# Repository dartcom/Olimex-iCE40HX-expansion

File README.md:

# Olimex-iCE40HX-expansion
An expansion board for the iCE40HX8K-EVB fpga devkit containing a 24-bit parallel video output, a VGA output and a dual composite input based on the ADV7180 SDTV video decoder.

# Resources
- VGA subsystem is based on the [Digilent Pmod VGA adapter](https://digilent.com/shop/pmod-vga-video-graphics-array/).

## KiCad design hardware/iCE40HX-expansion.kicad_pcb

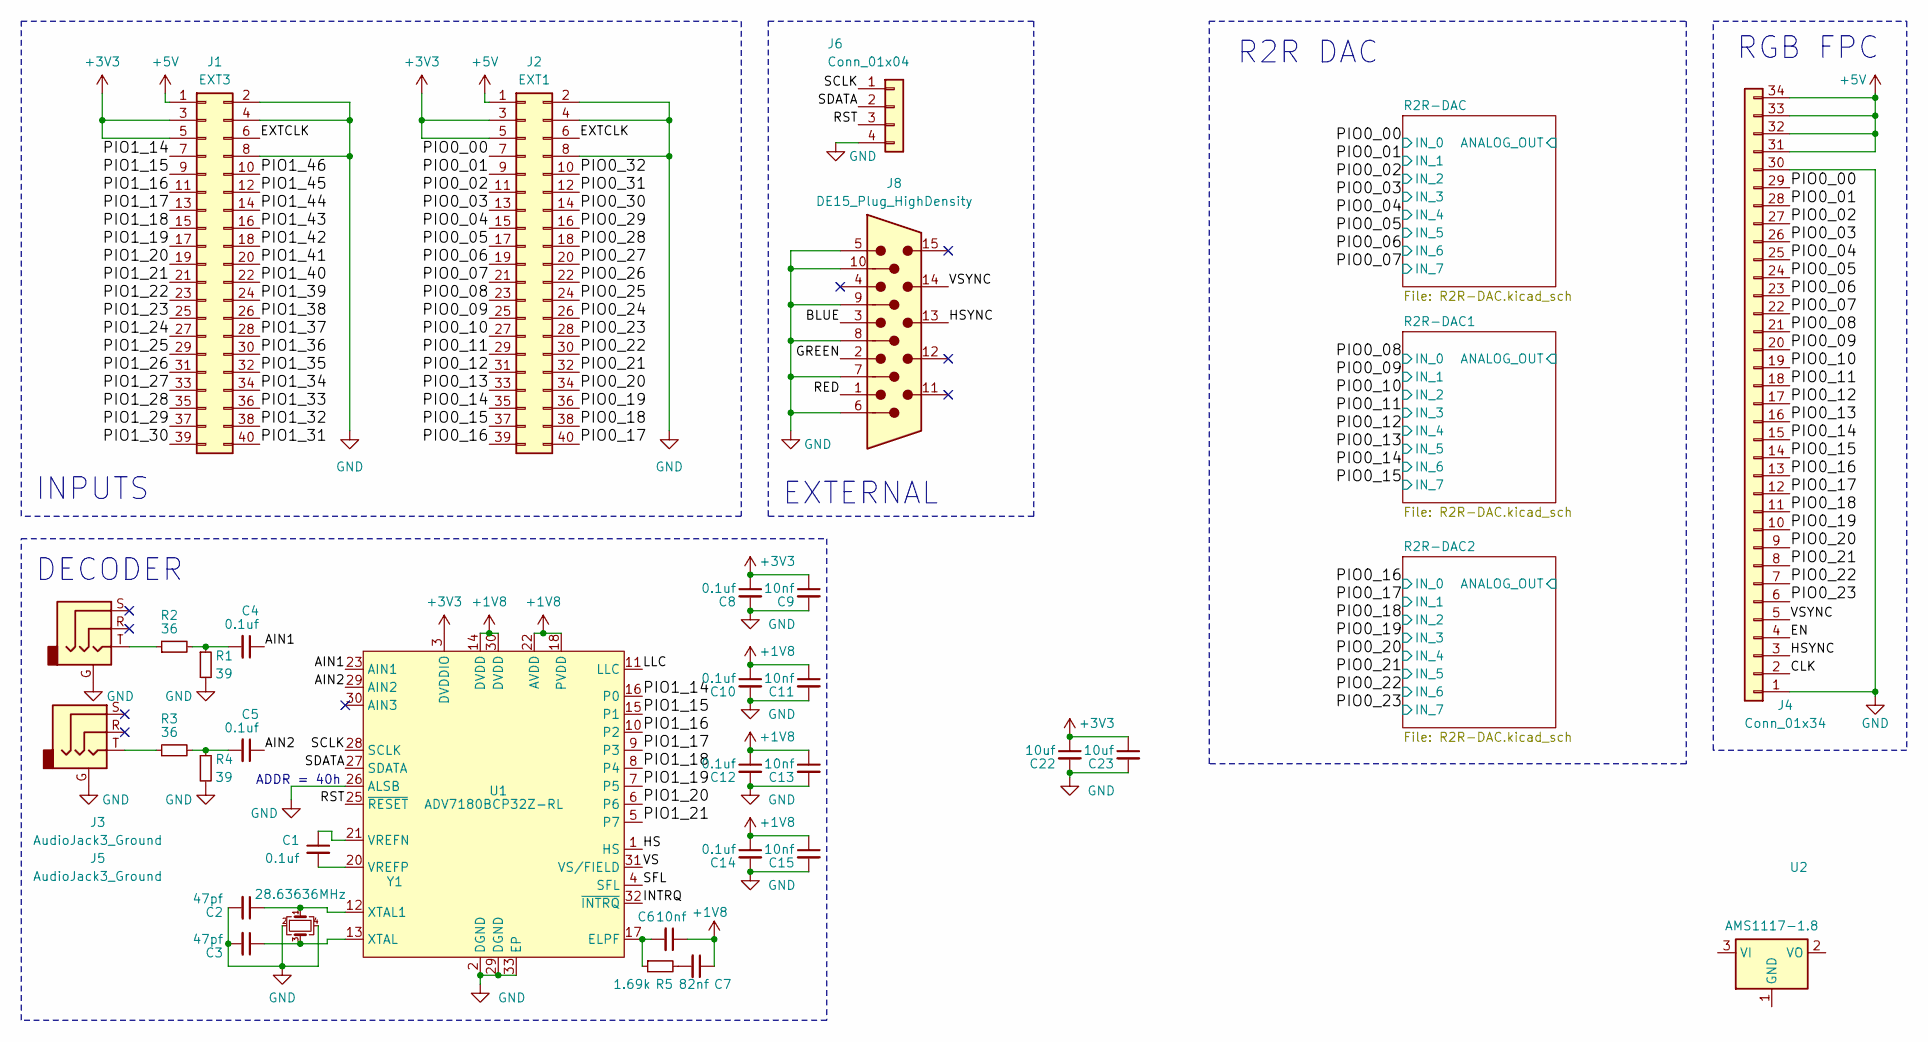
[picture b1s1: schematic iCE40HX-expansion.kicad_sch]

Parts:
C1, C4, C5, C8, C10, C12, C14: 0.1uf; C_0603_1608Metric
C2, C3: 47pf; C_0603_1608Metric
C6, C9, C11, C13, C15: 10nf; C_0603_1608Metric
C7: 82nf; C_0603_1608Metric
C22, C23: 10uf; C_0603_1608Metric
J1: EXT3; PinSocket_2x20_P1.27mm_Vertical_SMD
J2: EXT1; PinSocket_2x20_P1.27mm_Vertical_SMD
J3, J5: AudioJack3_Ground; Jack_3.5mm_KoreanHropartsElec_PJ-320D-4A_Horizontal
J4: Conn_01x34; FPC-SMD_KH-FG0.5-H2.0-34PIN
J6: Conn_01x04; PinHeader_1x04_P2.54mm_Vertical
J8: DE15_Plug_HighDensity; DSUB-TH_HYC06-HDR15B-060
R1, R4: 39; R_0603_1608Metric
R2, R3: 36; R_0603_1608Metric
R5: 1.69k; R_0603_1608Metric
U1: ADV7180BCP32Z-RL; LFCSP-32_L5.0-W5.0-P0.50-BL-EP3.6; LCSC Part C459884
U2: AMS1117-1.8; SOT-223-3_TabPin2
Y1: 28.63636MHz; Crystal_SMD_Abracon_ABM8AIG-4Pin_3.2x2.5mm

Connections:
+1V8: C6.1, C7.1, C10.1, C11.1, C12.1, C13.1, C14.1, C15.1, U1.14 (DVDD), U1.18 (PVDD), U1.22 (AVDD), U1.30 (DVDD)
+3V3: C8.1, C9.1, C22.1, C23.1, J1.3, J1.5, J2.3, J2.5, U1.3 (DVDDIO); also elsewhere on the board
+5V: J1.1, J2.1, J4.31, J4.32, J4.33, J4.34
/AIN1: C4.1, U1.23 (AIN1)
/BLUE: J8.3; also elsewhere on the board
/CLK: J4.2
/EN: J4.4
/EXTCLK: J1.6, J2.6
/GREEN: J8.2; also elsewhere on the board
/HS: U1.1 (HS)
/HSYNC: J4.3, J8.13
/INTRQ: U1.32 (~INTRQ)
/LLC: U1.11 (LLC)
/PIO0_00: J2.7, J4.29; also elsewhere on the board
/PIO0_01: J2.9, J4.28; also elsewhere on the board
/PIO0_02: J2.11, J4.27; also elsewhere on the board
/PIO0_03: J2.13, J4.26; also elsewhere on the board
/PIO0_04: J2.15, J4.25; also elsewhere on the board
/PIO0_05: J2.17, J4.24; also elsewhere on the board
/PIO0_06: J2.19, J4.23; also elsewhere on the board
/PIO0_07: J2.21, J4.22; also elsewhere on the board
/PIO0_08: J2.23, J4.21; also elsewhere on the board
/PIO0_09: J2.25, J4.20; also elsewhere on the board
/PIO0_10: J2.27, J4.19; also elsewhere on the board
/PIO0_11: J2.29, J4.18; also elsewhere on the board
/PIO0_12: J2.31, J4.17; also elsewhere on the board
/PIO0_13: J2.33, J4.16; also elsewhere on the board
/PIO0_14: J2.35, J4.15; also elsewhere on the board
/PIO0_15: J2.37, J4.14; also elsewhere on the board
/PIO0_16: J2.39, J4.13; also elsewhere on the board
/PIO0_17: J2.40, J4.12; also elsewhere on the board
/PIO0_18: J2.38, J4.11; also elsewhere on the board
/PIO0_19: J2.36, J4.10; also elsewhere on the board
/PIO0_20: J2.34, J4.9; also elsewhere on the board
/PIO0_21: J2.32, J4.8; also elsewhere on the board
/PIO0_22: J2.30, J4.7; also elsewhere on the board
/PIO0_23: J2.28, J4.6; also elsewhere on the board
/PIO0_24: J2.26
/PIO0_25: J2.24
/PIO0_26: J2.22
/PIO0_27: J2.20
/PIO0_28: J2.18
/PIO0_29: J2.16
/PIO0_30: J2.14
/PIO0_31: J2.12
/PIO0_32: J2.10
/PIO1_14: J1.7, U1.16 (P0)
/PIO1_15: J1.9, U1.15 (P1)
/PIO1_16: J1.11, U1.10 (P2)
/PIO1_17: J1.13, U1.9 (P3)
/PIO1_18: J1.15, U1.8 (P4)
/PIO1_19: J1.17, U1.7 (P5)
/PIO1_20: J1.19, U1.6
/PIO1_21: J1.21, U1.5 (P7)
/PIO1_22: J1.23
/PIO1_23: J1.25
/PIO1_24: J1.27
/PIO1_25: J1.29
/PIO1_26: J1.31
/PIO1_27: J1.33
/PIO1_28: J1.35
/PIO1_29: J1.37
/PIO1_30: J1.39
/PIO1_31: J1.40
/PIO1_32: J1.38
/PIO1_33: J1.36
/PIO1_34: J1.34
/PIO1_35: J1.32
/PIO1_36: J1.30
/PIO1_37: J1.28
/PIO1_38: J1.26
/PIO1_39: J1.24
/PIO1_40: J1.22
/PIO1_41: J1.20
/PIO1_42: J1.18
/PIO1_43: J1.16
/PIO1_44: J1.14
/PIO1_45: J1.12
/PIO1_46: J1.10
/RED: J8.1; also elsewhere on the board
/RST: J6.3, U1.25 (~RESET)
/SCLK: J6.1, U1.28 (SCLK)
/SDATA: J6.2, U1.27 (SDATA)
/SFL: U1.4 (SFL)
/VS: U1.31 (VS/FIELD)
/VSYNC: J4.5, J8.14
unnamed: C4.2, R1.1, R2.2
unnamed: C5.2, R3.2, R4.1
unnamed: C7.2, R5.2
unnamed: J3.T, R2.1
unnamed: J5.T, R3.1
unnamed: C6.2, R5.1, U1.17 (ELPF)
unnamed: C1.1, U1.21 (VREFN)
unnamed: C1.2, U1.20 (VREFP)
unnamed: C2.1, U1.12 (XTAL1), Y1.1
unnamed: C3.1, U1.13 (XTAL), Y1.3

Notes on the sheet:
EXTERNAL
R2R DAC
ADDR = 40h
RGB FPC
DECODER
INPUTS

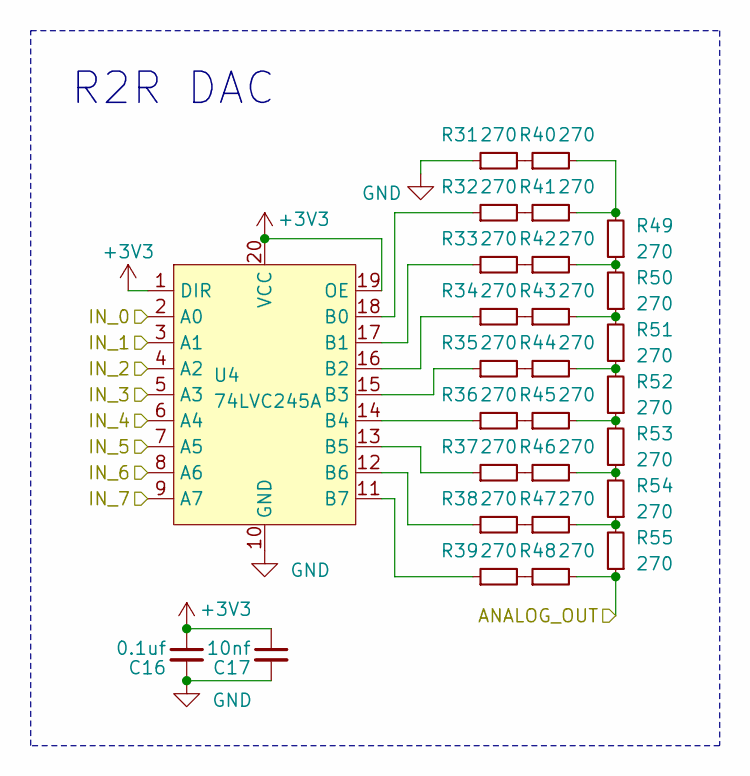
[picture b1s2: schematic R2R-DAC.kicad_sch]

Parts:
C16: 0.1uf; C_0603_1608Metric
C17: 10nf; C_0603_1608Metric
R31, R32, R33, R34, R35, R36, R37, R38, R39, R40, R41, R42, R43, R44, R45, R46, R47, R48, R49, R50, R51, R52, R53, R54, R55: 270; R_0603_1608Metric
U4: 74LVC245A; TSSOP-20_4.4x6.5mm_P0.65mm

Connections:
+3V3: C16.1, C17.1, U4.1 (DIR), U4.19 (OE), U4.20 (VCC); also elsewhere on the board
/BLUE: R48.2, R55.1; also elsewhere on the board
/PIO0_16: U4.2 (A0); also elsewhere on the board
/PIO0_17: U4.3 (A1); also elsewhere on the board
/PIO0_18: U4.4 (A2); also elsewhere on the board
/PIO0_19: U4.5 (A3); also elsewhere on the board
/PIO0_20: U4.6 (A4); also elsewhere on the board
/PIO0_21: U4.7 (A5); also elsewhere on the board
/PIO0_22: U4.8 (A6); also elsewhere on the board
/PIO0_23: U4.9 (A7); also elsewhere on the board
unnamed: R31.2, R40.1
unnamed: R32.2, R41.1
unnamed: R33.2, R42.1
unnamed: R34.2, R43.1
unnamed: R35.2, R44.1
unnamed: R36.2, R45.1
unnamed: R37.2, R46.1
unnamed: R38.2, R47.1
unnamed: R39.2, R48.1
unnamed: R40.2, R41.2, R49.2
unnamed: R42.2, R49.1, R50.2
unnamed: R43.2, R50.1, R51.2
unnamed: R44.2, R51.1, R52.2
unnamed: R45.2, R52.1, R53.2
unnamed: R46.2, R53.1, R54.2
unnamed: R47.2, R54.1, R55.2
unnamed: R32.1, U4.18 (B0)
unnamed: R33.1, U4.17 (B1)
unnamed: R34.1, U4.16 (B2)
unnamed: R35.1, U4.15 (B3)
unnamed: R36.1, U4.14 (B4)
unnamed: R37.1, U4.13 (B5)
unnamed: R38.1, U4.12 (B6)
unnamed: R39.1, U4.11 (B7)

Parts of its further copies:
C18, C20: 0.1uf; C_0603_1608Metric
C19, C21: 10nf; C_0603_1608Metric
R6, R7, R8, R9, R10, R11, R12, R13, R14, R15, R16, R17, R18, R19, R20, R21, R22, R23, R24, R25, R26, R27, R28, R29, R30, R81, R82, R83, R84, R85, R86, R87, R88, R89, R90, R91, R92, R93, R94, R95, R96, R97, R98, R99, R100, R101, R102, R103, R104, R105: 270; R_0603_1608Metric
U3, U6: 74LVC245A; TSSOP-20_4.4x6.5mm_P0.65mm

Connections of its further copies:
+3V3: C18.1, C19.1, C20.1, C21.1, U3.1 (DIR), U3.19 (OE), U3.20 (VCC), U6.1 (DIR), U6.19 (OE), U6.20 (VCC); also elsewhere on the board
/GREEN: R23.2, R30.1; also elsewhere on the board
/PIO0_00: U6.2 (A0); also elsewhere on the board
/PIO0_01: U6.3 (A1); also elsewhere on the board
/PIO0_02: U6.4 (A2); also elsewhere on the board
/PIO0_03: U6.5 (A3); also elsewhere on the board
/PIO0_04: U6.6 (A4); also elsewhere on the board
/PIO0_05: U6.7 (A5); also elsewhere on the board
/PIO0_06: U6.8 (A6); also elsewhere on the board
/PIO0_07: U6.9 (A7); also elsewhere on the board
/PIO0_08: U3.2 (A0); also elsewhere on the board
/PIO0_09: U3.3 (A1); also elsewhere on the board
/PIO0_10: U3.4 (A2); also elsewhere on the board
/PIO0_11: U3.5 (A3); also elsewhere on the board
/PIO0_12: U3.6 (A4); also elsewhere on the board
/PIO0_13: U3.7 (A5); also elsewhere on the board
/PIO0_14: U3.8 (A6); also elsewhere on the board
/PIO0_15: U3.9 (A7); also elsewhere on the board
/RED: R98.2, R105.1; also elsewhere on the board
unnamed: R10.2, R19.1
unnamed: R11.2, R20.1
unnamed: R12.2, R21.1
unnamed: R13.2, R22.1
unnamed: R14.2, R23.1
unnamed: R6.2, R15.1
unnamed: R15.2, R16.2, R24.2
unnamed: R7.2, R16.1
unnamed: R8.2, R17.1
unnamed: R17.2, R24.1, R25.2
unnamed: R9.2, R18.1
unnamed: R18.2, R25.1, R26.2
unnamed: R19.2, R26.1, R27.2
unnamed: R20.2, R27.1, R28.2
unnamed: R21.2, R28.1, R29.2
unnamed: R22.2, R29.1, R30.2
unnamed: R81.2, R90.1
unnamed: R82.2, R91.1
unnamed: R83.2, R92.1
unnamed: R84.2, R93.1
unnamed: R85.2, R94.1
unnamed: R86.2, R95.1
unnamed: R87.2, R96.1
unnamed: R88.2, R97.1
unnamed: R89.2, R98.1
unnamed: R90.2, R91.2, R99.2
unnamed: R93.2, R100.1, R101.2
unnamed: R92.2, R99.1, R100.2
unnamed: R94.2, R101.1, R102.2
unnamed: R95.2, R102.1, R103.2
unnamed: R96.2, R103.1, R104.2
unnamed: R97.2, R104.1, R105.2
unnamed: R7.1, U3.18 (B0)
unnamed: R8.1, U3.17 (B1)
unnamed: R9.1, U3.16 (B2)
unnamed: R10.1, U3.15 (B3)
unnamed: R11.1, U3.14 (B4)
unnamed: R12.1, U3.13 (B5)
unnamed: R13.1, U3.12 (B6)
unnamed: R14.1, U3.11 (B7)
unnamed: R82.1, U6.18 (B0)
unnamed: R83.1, U6.17 (B1)
unnamed: R84.1, U6.16 (B2)
unnamed: R85.1, U6.15 (B3)
unnamed: R86.1, U6.14 (B4)
unnamed: R87.1, U6.13 (B5)
unnamed: R88.1, U6.12 (B6)
unnamed: R89.1, U6.11 (B7)

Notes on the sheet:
R2R DAC

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
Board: 2 copper layers, 122 parts (0 on the bottom side), 129 nets, no tracks yet.

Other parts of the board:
C16#2, C18#2, C20#2: 0.1uf; C_0603_1608Metric
C17#2, C19#2, C21#2: 10nf; C_0603_1608Metric

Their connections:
+3V3: C16#2.1, C17#2.1, C18#2.1, C19#2.1, C20#2.1, C21#2.1; also elsewhere on the board

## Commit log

2023-11-01 initial push
2023-11-21 porgress with schematic
2023-11-22 moved R2R dacs into hierarchical sheets
2023-11-22 minor tweaks
2023-11-22 finished component placement
2023-11-27 continuation
2023-12-05 version 1.0
2024-03-20 fixed error in sync buffer OE pin
2024-05-30 srarting version 2
2024-05-31 progress
2025-05-06 backup
